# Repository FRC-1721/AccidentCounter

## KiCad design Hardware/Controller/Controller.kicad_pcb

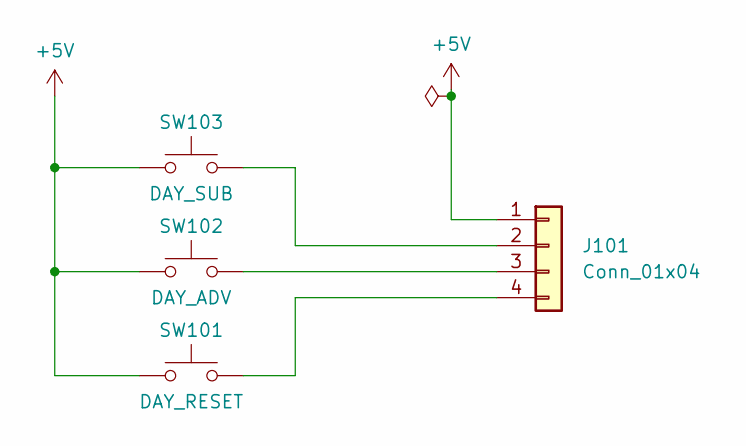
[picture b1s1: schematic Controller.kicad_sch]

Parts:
J101: Conn_01x04; SolderWire-1sqmm_1x04_P5.4mm_D1.4mm_OD2.7mm_Relief
SW101: DAY_RESET; SW_PUSH_6mm_H5mm
SW102: DAY_ADV; SW_PUSH_6mm_H5mm
SW103: DAY_SUB; SW_PUSH_6mm_H5mm

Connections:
+5V: J101.1, SW101.1, SW102.1, SW103.1
unnamed: J101.2, SW103.2
unnamed: J101.3, SW102.2
unnamed: J101.4, SW101.2

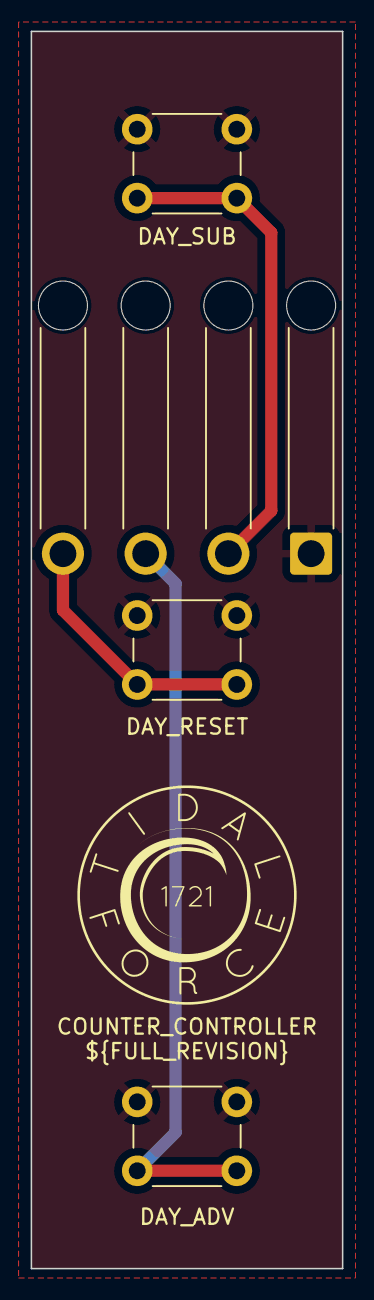
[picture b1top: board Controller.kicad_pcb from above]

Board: 2 copper layers, 20.3 x 80.8 mm, 4 parts (0 on the bottom side), 4 nets.

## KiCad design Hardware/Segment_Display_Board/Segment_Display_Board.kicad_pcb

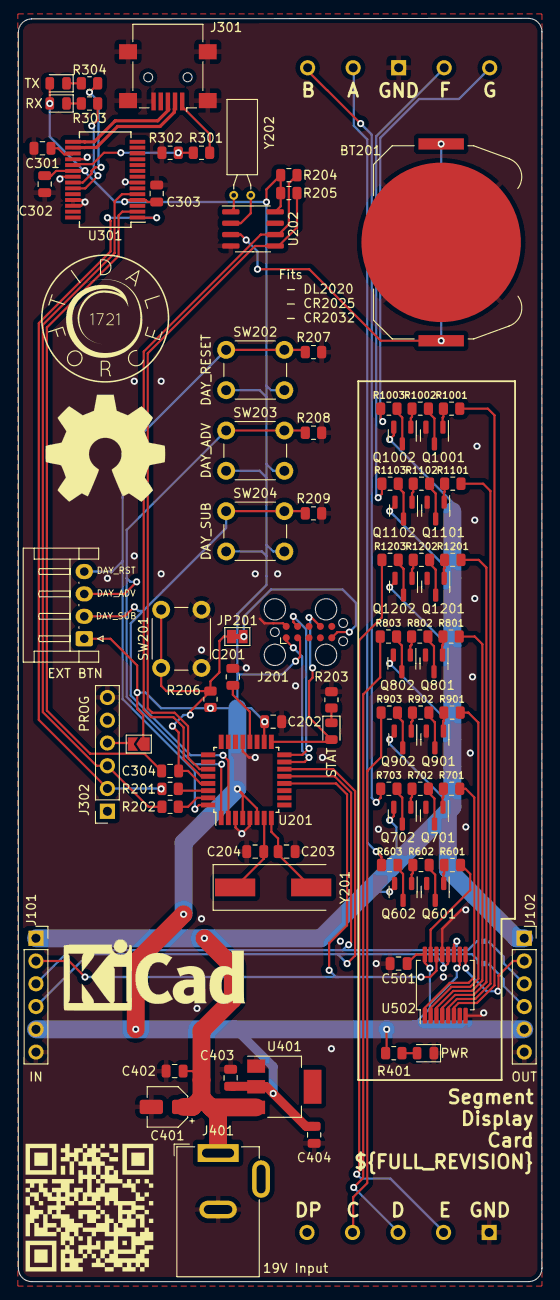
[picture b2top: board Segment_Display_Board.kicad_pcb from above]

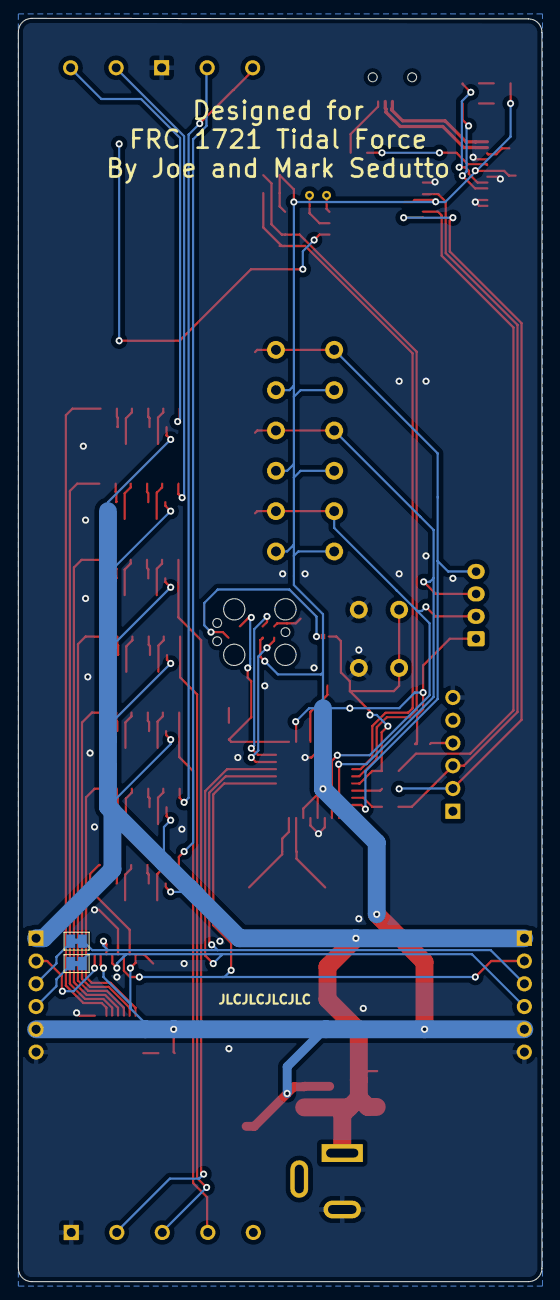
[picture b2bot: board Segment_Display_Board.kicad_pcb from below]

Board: 2 copper layers, 58.4 x 141.0 mm, 90 parts (2 on the bottom side), 84 nets.

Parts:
BT201: 3v; BatteryHolder_Keystone_3034_1x20mm
C201, C202: 100nf; C_0805_2012Metric
C203, C204: 22pf; C_0805_2012Metric
C301, C302, C303, C304, C402, C403, C501: 100nF; C_0805_2012Metric
C401: 10uf; CP_Elec_4x3
C404: 1uF; C_0805_2012Metric
D201: STAT; LED_0805_2012Metric
D301: RX; LED_0805_2012Metric
D302: TX; LED_0805_2012Metric
D401: PWR; LED_0805_2012Metric
J101: IN; PinSocket_1x06_P2.54mm_Vertical
J102: OUT; PinSocket_1x06_P2.54mm_Vertical
J201: Tag Connect; Tag-Connect_TC2050-IDC-FP_2x05_P1.27mm_Vertical
J202: EXT BTN; JST_EH_S4B-EH_1x04_P2.50mm_Horizontal
J301: USB_B_Micro; USB_Mini-B_Lumberg_2486_01_Horizontal
J302: PROG; PinSocket_1x06_P2.54mm_Vertical
J401: 19V Input; BarrelJack_GCT_DCJ200-10-A_Horizontal
JP201: RSTBridge; SolderJumper-2_P1.3mm_Bridged_Pad1.0x1.5mm
JP301: SolderJumper_2_Open; SolderJumper-2_P1.3mm_Open_TrianglePad1.0x1.5mm
JP501, JP502: SolderJumper_2_Bridged; SolderJumper-2_P1.3mm_Bridged_Pad1.0x1.5mm
Q601, Q701, Q801, Q901, Q1001, Q1101, Q1201: MMBT3904; SOT-23
Q602, Q702, Q802, Q902, Q1002, Q1102, Q1202: MMBT3906; SOT-23
R201, R202, R203, R206, R303, R304, R401: 1K; R_0805_2012Metric
R204, R205, R207, R208, R209, R302, R601, R701, R801, R901, R1001, R1101, R1201: 10K; R_0805_2012Metric
R301: 4K7; R_0805_2012Metric
R602, R702, R802, R902, R1002, R1102, R1202: 2K2; R_0805_2012Metric
R603, R703, R803, R903, R1003, R1103, R1203: 680R; R_0805_2012Metric
SW201: RESET; SW_PUSH_6mm_H5mm
SW202: DAY_RESET; SW_PUSH_6mm_H5mm
SW203: DAY_ADV; SW_PUSH_6mm_H5mm
SW204: DAY_SUB; SW_PUSH_6mm_H5mm
U201: ATmega328P-A; TQFP-32_7x7mm_P0.8mm
U202: DS1307Z+; SOIC-8_3.9x4.9mm_P1.27mm
U301: FT232RL; SSOP-28_5.3x10.2mm_P0.65mm
U401: NCV1117ST50T3G; SOT-223
U501: 5inSegment
U502: SN74HC595
Y201: 16mHz; Crystal_SMD_HC49-SD
Y202: 32.768kHz; Crystal_C38-LF_D3.0mm_L8.0mm_Horizontal

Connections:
+3.3V: C301.1, U301.17 (3V3OUT)
+5V: C202.1, C302.1, C303.1, C403.1, C404.1, C501.1, D301.2 (A), D302.2 (A), J101.5, J102.5, J201.2, J202.1, JP301.1 (A), R204.1, R205.1, R206.1, R401.1, SW202.2, SW203.2, SW204.2, U201.4 (VCC), U201.6 (VCC), U201.18 (AVCC), U202.8 (VCC), U301.4 (VCCIO), U301.20 (VCC), U401.2 (VO), U502.10 (SRCLR), U502.16 (VCC)
+19V: C401.1, C402.1, J101.1, J102.1, J401.1, Q602.2 (E), Q702.2 (E), Q802.2 (E), Q902.2 (E), Q1002.2 (E), Q1102.2 (E), Q1202.2 (E), U401.3 (VI)
/C_OUT: J101.3, JP502.1 (A), U201.13 (PB1), U502.11 (SRCLK)
/D_OUT: J101.2, U201.12 (PB0), U502.14 (SER)
/Display Card/CLOCK_OUT: J102.3, JP502.2 (B)
/Display Card/DATA_OUT: J102.2, U502.9 (QH')
/Display Card/LATCH_OUT: J102.4, JP501.2 (B)
/Display Card/SEG_A: R601.1, U502.15 (QA)
/Display Card/SEG_A_LAMP: R603.2, U501.2 (A)
/Display Card/SEG_B: R701.1, U502.1 (QB)
/Display Card/SEG_B_LAMP: R703.2, U501.1 (B)
/Display Card/SEG_C: R901.1, U502.2 (QC)
/Display Card/SEG_C_LAMP: R903.2, U501.7 (C)
/Display Card/SEG_D: R801.1, U502.3 (QD)
/Display Card/SEG_D_LAMP: R803.2, U501.8 (D)
/Display Card/SEG_E: R1201.1, U502.4 (QE)
/Display Card/SEG_E_LAMP: R1203.2, U501.9 (E)
/Display Card/SEG_F: R1101.1, U502.5 (QF)
/Display Card/SEG_F_LAMP: R1103.2, U501.4 (F)
/Display Card/SEG_G: R1001.1, U502.6 (QG)
/Display Card/SEG_G_LAMP: R1003.2, U501.5 (G)
/L_OUT: J101.4, JP501.1 (A), U201.14 (PB2), U502.12 (RCLK)
/MCU/DAY_ADVANCE: J202.3, R208.1, SW203.1, U201.1 (PD3)
/MCU/DAY_RESET: J202.4, R207.1, SW202.1, U201.32 (PD2)
/MCU/DAY_SUBTRACT: J202.2, R209.1, SW204.1, U201.2 (PD4)
/MCU/ICSP_MISO: J201.9, U201.16 (PB4)
/MCU/ICSP_MOSI: J201.1, U201.15 (PB3)
/MCU/ICSP_RST: J201.5, JP201.2 (B)
/MCU/ICSP_SCK: D201.2 (A), J201.7, U201.17 (PB5)
/MCU/RST: C304.1, JP201.1 (A), R206.2, SW201.1, U201.29 (~RESET/PC6)
/MCU/RXD: J302.2, R201.2, U301.1 (TXD)
/MCU/SCL: R204.2, U201.28 (PC5), U202.6 (SCL)
/MCU/SDA: R205.2, U201.27 (PC4), U202.5 (SDA)
/MCU/TXD: J302.3, R202.2, U301.5 (RXD)
/USB/USB+: J301.3 (D+), U301.15 (USBD+)
/USB/USB-: J301.2 (D-), U301.16 (USBD-)
GND: BT201.2 (-), C201.2, C202.2, C203.2, C204.2, C301.2, C302.2, C303.2, C401.2, C402.2, C403.2, C404.2, C501.2, D401.1 (K), J101.6, J102.6, J201.10, J301.5 (GND), J301.6 (Shield), J302.6, J401.2, Q601.2 (E), Q701.2 (E), Q801.2 (E), Q901.2 (E), Q1001.2 (E), Q1101.2 (E), Q1201.2 (E), R203.1, R207.2, R208.2, R209.2, R302.1, SW201.2, U201.3 (GND), U201.5 (GND), U201.21 (GND), U202.4 (GND), U301.7 (GND), U301.18 (GND), U301.21 (GND), U301.25 (AGND), U301.26 (TEST), U401.1 (GND), U501.3 (GND), U501.10 (GND), U502.8 (GND), U502.13 (OE)
unnamed: BT201.1 (+), U202.3 (VBAT)
unnamed: C201.1, U201.20 (AREF)
unnamed: C203.1, U201.8 (XTAL2/PB7), Y201.2
unnamed: C204.1, U201.7 (XTAL1/PB6), Y201.1
unnamed: C304.2, U301.2 (DTR)
unnamed: D201.1 (K), R203.2
unnamed: D301.1 (K), R303.2
unnamed: D302.1 (K), R304.1
unnamed: D401.2 (A), R401.2
unnamed: J302.4, JP301.2 (B)
unnamed: Q601.1 (B), R601.2
unnamed: Q601.3 (C), R602.1
unnamed: Q602.1 (B), R602.2
unnamed: Q602.3 (C), R603.1
unnamed: Q701.1 (B), R701.2
unnamed: Q701.3 (C), R702.1
unnamed: Q702.1 (B), R702.2
unnamed: Q702.3 (C), R703.1
unnamed: Q801.1 (B), R801.2
unnamed: Q801.3 (C), R802.1
unnamed: Q802.1 (B), R802.2
unnamed: Q802.3 (C), R803.1
unnamed: Q901.1 (B), R901.2
unnamed: Q901.3 (C), R902.1
unnamed: Q902.1 (B), R902.2
unnamed: Q902.3 (C), R903.1
unnamed: Q1001.1 (B), R1001.2
unnamed: Q1001.3 (C), R1002.1
unnamed: Q1002.1 (B), R1002.2
unnamed: Q1002.3 (C), R1003.1
unnamed: Q1101.1 (B), R1101.2
unnamed: Q1101.3 (C), R1102.1
unnamed: Q1102.1 (B), R1102.2
unnamed: Q1102.3 (C), R1103.1
unnamed: Q1201.1 (B), R1201.2
unnamed: Q1201.3 (C), R1202.1
unnamed: Q1202.1 (B), R1202.2
unnamed: Q1202.3 (C), R1203.1
unnamed: R201.1, U201.30 (PD0)
unnamed: R202.1, U201.31 (PD1)
unnamed: R301.1, R302.2, U301.19 (~RESET)
unnamed: R303.1, U301.23 (CBUS0)
unnamed: R304.2, U301.22 (CBUS1)
unnamed: U202.1 (X1), Y202.2
unnamed: U202.2 (X2), Y202.1
VBUS: J301.1 (VBUS), R301.2

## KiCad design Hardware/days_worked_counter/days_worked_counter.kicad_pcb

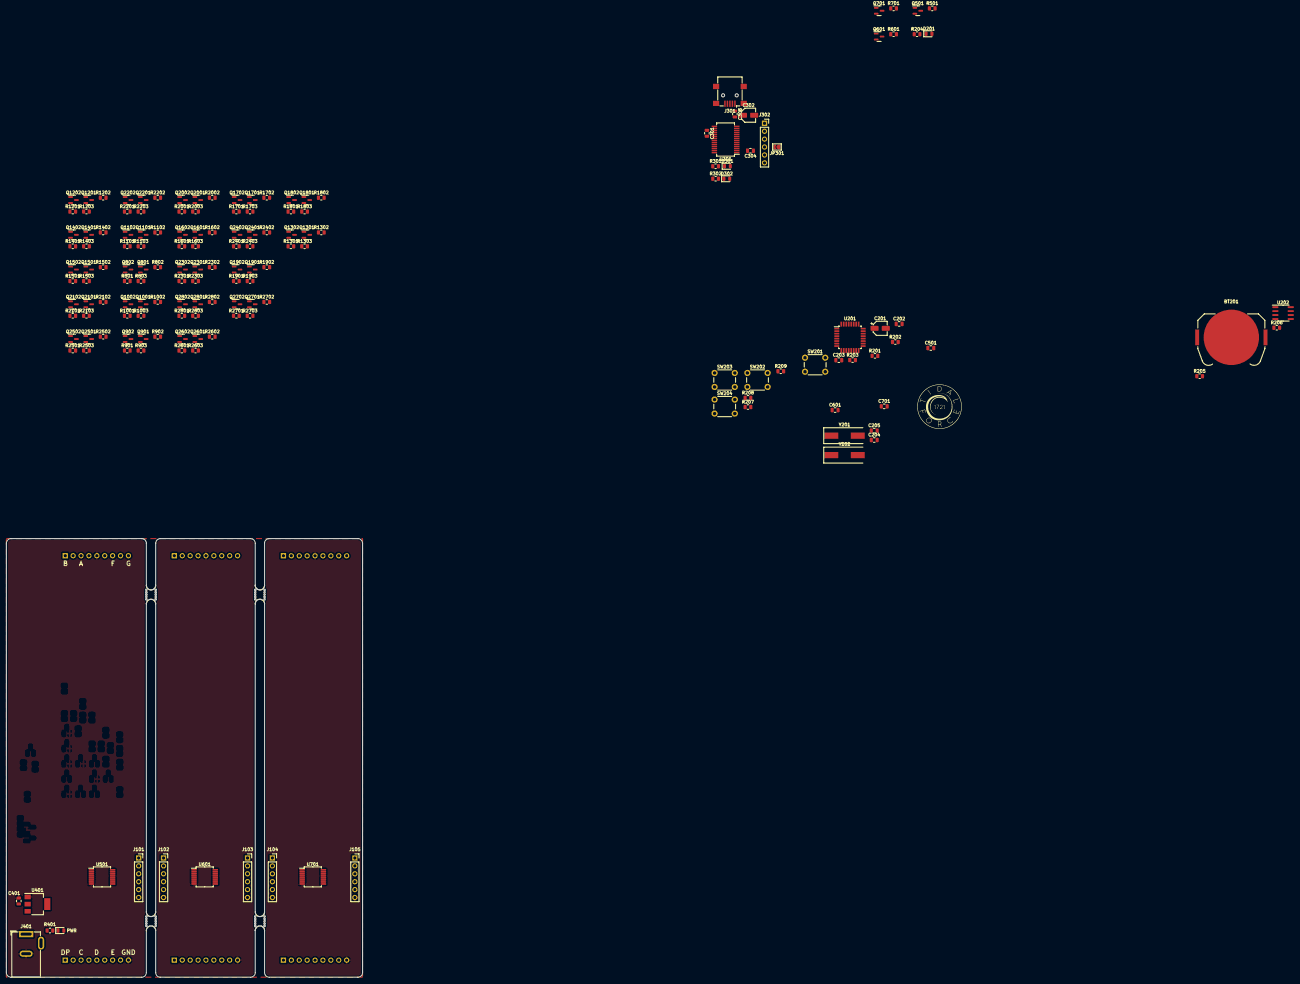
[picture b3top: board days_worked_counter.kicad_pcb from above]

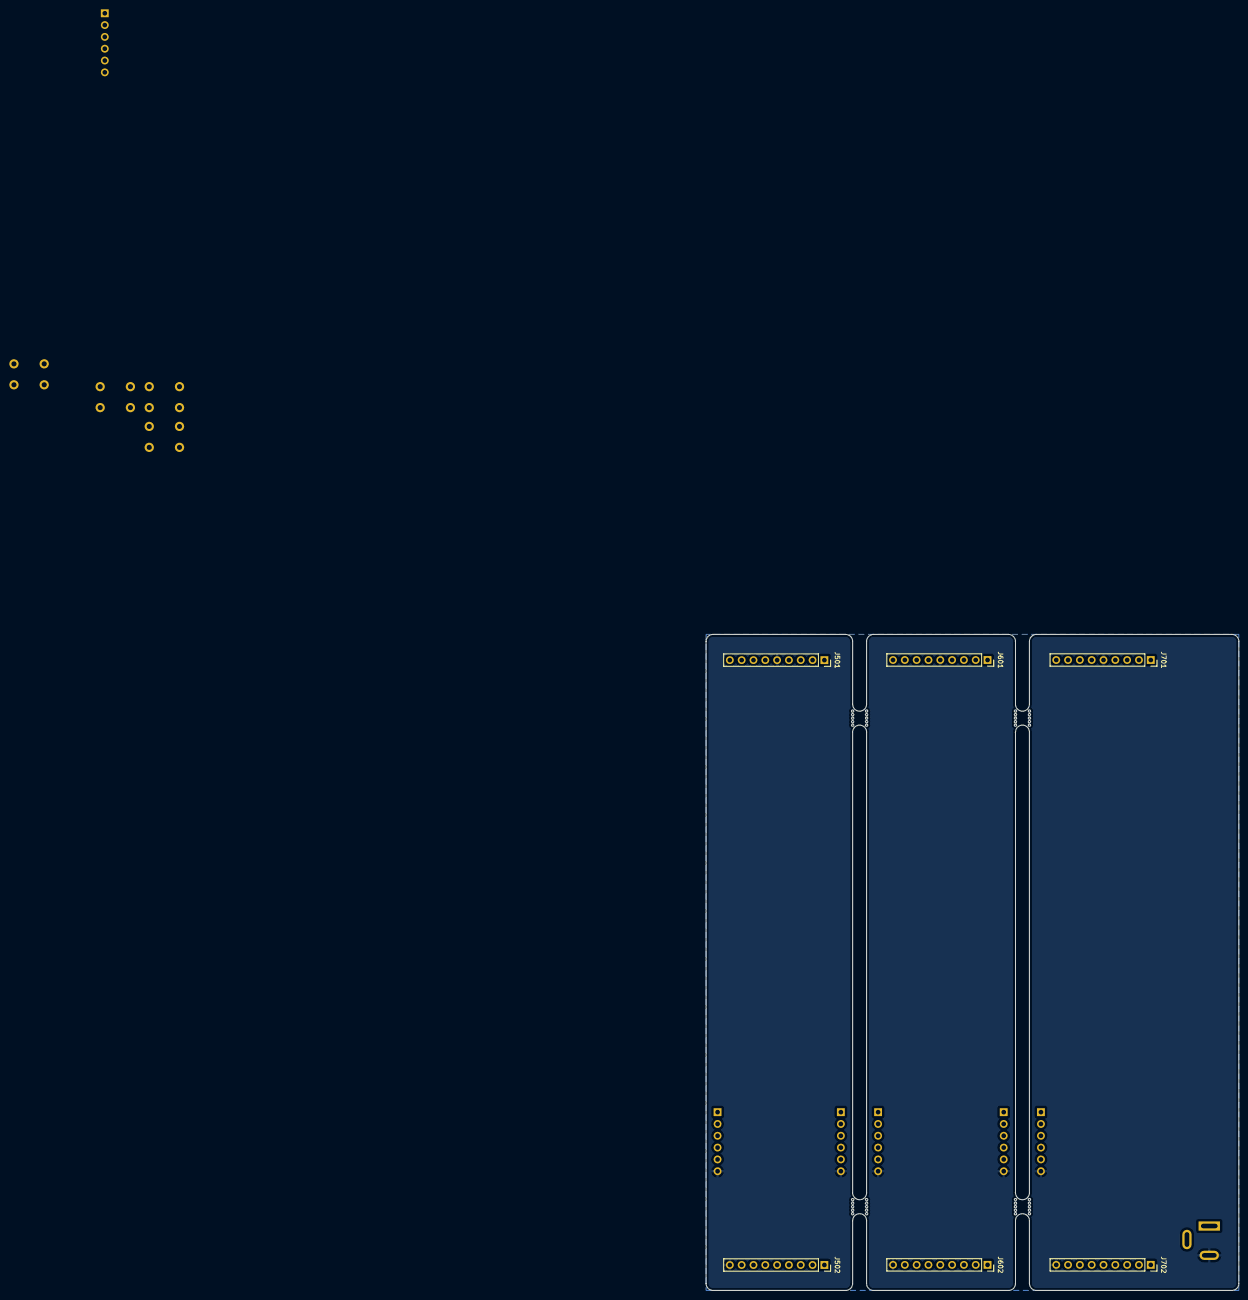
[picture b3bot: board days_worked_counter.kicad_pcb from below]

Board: 2 copper layers, 114.5 x 141.0 mm, 173 parts (6 on the bottom side), 170 nets, no tracks yet.

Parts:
BT201: 3v; BatteryHolder_Keystone_3034_1x20mm
C201, C302: 4.7uf; CP_Elec_4x3
C202, C203, C303: 100nf; C_0805_2012Metric
C204, C205: 22pf; C_0805_2012Metric
C301, C304, C401: 100nF; C_0805_2012Metric
C501, C601, C701: 10uF; C_0805_2012Metric
D201: STAT; LED_0805_2012Metric
D301: RX; LED_0805_2012Metric
D302: TX; LED_0805_2012Metric
D401: PWR; LED_0805_2012Metric
J101, J103, J105: OUT; PinSocket_1x06_P2.54mm_Vertical
J102, J104: IN; PinSocket_1x06_P2.54mm_Vertical
J301: USB_B_Micro; USB_Mini-B_Lumberg_2486_01_Horizontal
J302: PROG; PinSocket_1x06_P2.54mm_Vertical
J401: 19V Input; BarrelJack_GCT_DCJ200-10-A_Horizontal
J501, J601, J701: Top Conn; PinSocket_1x09_P2.54mm_Vertical
J502, J602, J702: Bottom Conn; PinSocket_1x09_P2.54mm_Vertical
JP301: SolderJumper_2_Open; SolderJumper-2_P1.3mm_Open_TrianglePad1.0x1.5mm
Q501, Q601, Q701, Q801, Q901, Q1001, Q1101, Q1201, Q1301, Q1401, Q1501, Q1601, Q1701, Q1801, Q1901, Q2001, Q2101, Q2201, Q2301, Q2401, Q2501, Q2601, Q2701, Q2801: MMBT3904; SOT-23
Q802, Q902, Q1002, Q1102, Q1202, Q1302, Q1402, Q1502, Q1602, Q1702, Q1802, Q1902, Q2002, Q2102, Q2202, Q2302, Q2402, Q2502, Q2602, Q2702, Q2802: MMBT3906; SOT-23
R201, R202, R203, R204, R301, R302, R401: 1K; R_0805_2012Metric
R205, R206, R207, R208, R209, R501, R601, R701, R801, R901, R1001, R1101, R1201, R1301, R1401, R1501, R1601, R1701, R1801, R1901, R2001, R2101, R2201, R2301, R2401, R2501, R2601, R2701, R2801: 10K; R_0805_2012Metric
R802, R902, R1002, R1102, R1202, R1302, R1402, R1502, R1602, R1702, R1802, R1902, R2002, R2102, R2202, R2302, R2402, R2502, R2602, R2702, R2802: 2K2; R_0805_2012Metric
R803, R903, R1003, R1103, R1203, R1303, R1403, R1503, R1603, R1703, R1803, R1903, R2003, R2103, R2203, R2303, R2403, R2503, R2603, R2703, R2803: 250R; R_0805_2012Metric
SW201: RESET; SW_PUSH_6mm_H5mm
SW202: DAY_RESET; SW_PUSH_6mm_H5mm
SW203: DAY_ADV; SW_PUSH_6mm_H5mm
SW204: DAY_SUB; SW_PUSH_6mm_H5mm
U201: ATmega328P-A; TQFP-32_7x7mm_P0.8mm
U202: DS1307Z+; SOIC-8_3.9x4.9mm_P1.27mm
U301: FT232RL; SSOP-28_5.3x10.2mm_P0.65mm
U401: LM1117-5.0; SOT-223
U501, U601, U701: SN74HC595
Y201: 16mHz; Crystal_SMD_HC49-SD
Y202: 32.768kHz; Crystal_SMD_HC49-SD
mouse-bite-3mm-slot, mouse-bite-3mm-slot#2, mouse-bite-3mm-slot#3, mouse-bite-3mm-slot#4: VAL**; mouse-bite-3mm-slot

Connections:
+3V3: C301.1, U301.17 (3V3OUT)
+5V: C201.1, C203.1, C401.1, C501.1, C601.1, C701.1, D301.2 (A), D302.2 (A), J101.5, J102.5, J103.5, J104.5, J105.5, JP301.1 (A), R201.1, R205.1, R206.1, R401.1, SW202.2, SW203.2, SW204.2, U201.4 (VCC), U201.6 (VCC), U201.18 (AVCC), U202.8 (VCC), U301.4 (VCCIO), U301.20 (VCC), U401.2 (VO), U501.10 (SRCLR), U501.16 (VCC), U601.10 (SRCLR), U601.16 (VCC), U701.10 (SRCLR), U701.16 (VCC)
+19V: J101.1, J102.1, J103.1, J104.1, J105.1, J401.1, Q802.2 (E), Q902.2 (E), Q1002.2 (E), Q1102.2 (E), Q1202.2 (E), Q1302.2 (E), Q1402.2 (E), Q1502.2 (E), Q1602.2 (E), Q1702.2 (E), Q1802.2 (E), Q1902.2 (E), Q2002.2 (E), Q2102.2 (E), Q2202.2 (E), Q2302.2 (E), Q2402.2 (E), Q2502.2 (E), Q2602.2 (E), Q2702.2 (E), Q2802.2 (E), U401.3 (VI)
/Display Card 0/CLOCK_IN: J101.3, U201.13 (PB1), U501.11 (SRCLK)
/Display Card 0/DATA_IN: U201.12 (PB0), U501.14 (SER)
/Display Card 0/DATA_OUT: J101.2, U501.9 (QH')
/Display Card 0/LATCH_IN: J101.4, U201.14 (PB2), U501.12 (RCLK)
/Display Card 0/SEG_A: R801.1, U501.15 (QA)
/Display Card 0/SEG_A_LAMP: J501.3, R803.2
/Display Card 0/SEG_B: Q501.1 (B), R501.1, R1101.1, U501.1 (QB)
/Display Card 0/SEG_B_LAMP: J501.1, R1103.2
/Display Card 0/SEG_C: R1501.1, U501.2 (QC)
/Display Card 0/SEG_C_LAMP: J502.3, R1503.2
/Display Card 0/SEG_D: R1401.1, U501.3 (QD)
/Display Card 0/SEG_D_LAMP: J502.5, R1403.2
/Display Card 0/SEG_E: R2201.1, U501.4 (QE)
/Display Card 0/SEG_E_LAMP: J502.7, R2203.2
/Display Card 0/SEG_F: R2101.1, U501.5 (QF)
/Display Card 0/SEG_F_LAMP: J501.7, R2103.2
/Display Card 0/SEG_G: R2001.1, U501.6 (QG)
/Display Card 0/SEG_G_LAMP: J501.9, R2003.2
/Display Card 1/CLOCK_IN: J102.3, J103.3, U601.11 (SRCLK)
/Display Card 1/DATA_IN: J102.2, U601.14 (SER)
/Display Card 1/DATA_OUT: J103.2, U601.9 (QH')
/Display Card 1/LATCH_IN: J102.4, J103.4, U601.12 (RCLK)
/Display Card 1/SEG_A: R901.1, U601.15 (QA)
/Display Card 1/SEG_A_LAMP: J601.3, R903.2
/Display Card 1/SEG_B: Q601.1 (B), R601.1, R1201.1, U601.1 (QB)
/Display Card 1/SEG_B_LAMP: J601.1, R1203.2
/Display Card 1/SEG_C: R1701.1, U601.2 (QC)
/Display Card 1/SEG_C_LAMP: J602.3, R1703.2
/Display Card 1/SEG_D: R1601.1, U601.3 (QD)
/Display Card 1/SEG_D_LAMP: J602.5, R1603.2
/Display Card 1/SEG_E: R2501.1, U601.4 (QE)
/Display Card 1/SEG_E_LAMP: J602.7, R2503.2
/Display Card 1/SEG_F: R2401.1, U601.5 (QF)
/Display Card 1/SEG_F_LAMP: J601.7, R2403.2
/Display Card 1/SEG_G: R2301.1, U601.6 (QG)
/Display Card 1/SEG_G_LAMP: J601.9, R2303.2
/Display Card 2/CLOCK_IN: J104.3, J105.3, U701.11 (SRCLK)
/Display Card 2/DATA_IN: J104.2, U701.14 (SER)
/Display Card 2/DATA_OUT: J105.2, U701.9 (QH')
/Display Card 2/LATCH_IN: J104.4, J105.4, U701.12 (RCLK)
/Display Card 2/SEG_A: R1001.1, U701.15 (QA)
/Display Card 2/SEG_A_LAMP: J701.3, R1003.2
/Display Card 2/SEG_B: Q701.1 (B), R701.1, R1301.1, U701.1 (QB)
/Display Card 2/SEG_B_LAMP: J701.1, R1303.2
/Display Card 2/SEG_C: R1901.1, U701.2 (QC)
/Display Card 2/SEG_C_LAMP: J702.3, R1903.2
/Display Card 2/SEG_D: R1801.1, U701.3 (QD)
/Display Card 2/SEG_D_LAMP: J702.5, R1803.2
/Display Card 2/SEG_E: R2801.1, U701.4 (QE)
/Display Card 2/SEG_E_LAMP: J702.7, R2803.2
/Display Card 2/SEG_F: R2701.1, U701.5 (QF)
/Display Card 2/SEG_F_LAMP: J701.7, R2703.2
/Display Card 2/SEG_G: R2601.1, U701.6 (QG)
/Display Card 2/SEG_G_LAMP: J701.9, R2603.2
/MCU/DAY_ADVANCE: R208.1, SW203.1, U201.1 (PD3)
/MCU/DAY_RESET: R207.1, SW202.1, U201.32 (PD2)
/MCU/DAY_SUBTRACT: R209.1, SW204.1, U201.2 (PD4)
/MCU/RST: C304.1, R201.2, SW201.1, U201.29 (~RESET/PC6)
/MCU/RXD: J302.2, R202.2, U301.1 (TXD)
/MCU/SCL: R205.2, U201.28 (PC5), U202.6 (SCL)
/MCU/SDA: R206.2, U201.27 (PC4), U202.5 (SDA)
/MCU/TXD: J302.3, R203.2, U301.5 (RXD)
GND: BT201.2 (-), C201.2, C202.2, C203.2, C204.2, C205.2, C301.2, C302.2, C303.2, C401.2, C501.2, C601.2, C701.2, D401.1 (K), J101.6, J102.6, J103.6, J104.6, J105.6, J301.5 (GND), J301.6 (Shield), J302.6, J401.2, J501.5, J502.9, J601.5, J602.9, J701.5, J702.9, Q501.2 (E), Q601.2 (E), Q701.2 (E), Q801.2 (E), Q901.2 (E), Q1001.2 (E), Q1101.2 (E), Q1201.2 (E), Q1301.2 (E), Q1401.2 (E), Q1501.2 (E), Q1601.2 (E), Q1701.2 (E), Q1801.2 (E), Q1901.2 (E), Q2001.2 (E), Q2101.2 (E), Q2201.2 (E), Q2301.2 (E), Q2401.2 (E), Q2501.2 (E), Q2601.2 (E), Q2701.2 (E), Q2801.2 (E), R204.1, R207.2, R208.2, R209.2, R501.2, R601.2, R701.2, SW201.2, U201.3 (GND), U201.5 (GND), U201.21 (GND), U202.4 (GND), U301.7 (GND), U301.18 (GND), U301.21 (GND), U301.25 (AGND), U301.26 (TEST), U401.1 (GND), U501.8 (GND), U501.13 (OE), U601.8 (GND), U601.13 (OE), U701.8 (GND), U701.13 (OE)
unnamed: BT201.1 (+), U202.3 (VBAT)
unnamed: C202.1, U201.20 (AREF)
unnamed: C204.1, U201.8 (XTAL2/PB7), Y201.2
unnamed: C205.1, U201.7 (XTAL1/PB6), Y201.1
unnamed: C304.2, U301.2 (DTR)
unnamed: D201.1 (K), R204.2
unnamed: D201.2 (A), U201.17 (PB5)
unnamed: D301.1 (K), R301.2
unnamed: D302.1 (K), R302.1
unnamed: D401.2 (A), R401.2
unnamed: J301.2 (D-), U301.16 (USBD-)
unnamed: J301.3 (D+), U301.15 (USBD+)
unnamed: J302.4, JP301.2 (B)
unnamed: Q801.1 (B), R801.2
unnamed: Q801.3 (C), R802.1
unnamed: Q802.1 (B), R802.2
unnamed: Q802.3 (C), R803.1
unnamed: Q901.1 (B), R901.2
unnamed: Q901.3 (C), R902.1
unnamed: Q902.1 (B), R902.2
unnamed: Q902.3 (C), R903.1
unnamed: Q1001.1 (B), R1001.2
unnamed: Q1001.3 (C), R1002.1
unnamed: Q1002.1 (B), R1002.2
unnamed: Q1002.3 (C), R1003.1
unnamed: Q1101.1 (B), R1101.2
unnamed: Q1101.3 (C), R1102.1
unnamed: Q1102.1 (B), R1102.2
unnamed: Q1102.3 (C), R1103.1
unnamed: Q1201.1 (B), R1201.2
unnamed: Q1201.3 (C), R1202.1
unnamed: Q1202.1 (B), R1202.2
unnamed: Q1202.3 (C), R1203.1
unnamed: Q1301.1 (B), R1301.2
unnamed: Q1301.3 (C), R1302.1
unnamed: Q1302.1 (B), R1302.2
unnamed: Q1302.3 (C), R1303.1
unnamed: Q1401.1 (B), R1401.2
unnamed: Q1401.3 (C), R1402.1
unnamed: Q1402.1 (B), R1402.2
unnamed: Q1402.3 (C), R1403.1
unnamed: Q1501.1 (B), R1501.2
unnamed: Q1501.3 (C), R1502.1
unnamed: Q1502.1 (B), R1502.2
unnamed: Q1502.3 (C), R1503.1
unnamed: Q1601.1 (B), R1601.2
unnamed: Q1601.3 (C), R1602.1
unnamed: Q1602.1 (B), R1602.2
unnamed: Q1602.3 (C), R1603.1
unnamed: Q1701.1 (B), R1701.2
unnamed: Q1701.3 (C), R1702.1
unnamed: Q1702.1 (B), R1702.2
unnamed: Q1702.3 (C), R1703.1
unnamed: Q1801.1 (B), R1801.2
unnamed: Q1801.3 (C), R1802.1
unnamed: Q1802.1 (B), R1802.2
unnamed: Q1802.3 (C), R1803.1
unnamed: Q1901.1 (B), R1901.2
unnamed: Q1901.3 (C), R1902.1
unnamed: Q1902.1 (B), R1902.2
unnamed: Q1902.3 (C), R1903.1
unnamed: Q2001.1 (B), R2001.2
unnamed: Q2001.3 (C), R2002.1
unnamed: Q2002.1 (B), R2002.2
unnamed: Q2002.3 (C), R2003.1
unnamed: Q2101.1 (B), R2101.2
unnamed: Q2101.3 (C), R2102.1
unnamed: Q2102.1 (B), R2102.2
unnamed: Q2102.3 (C), R2103.1
unnamed: Q2201.1 (B), R2201.2
unnamed: Q2201.3 (C), R2202.1
unnamed: Q2202.1 (B), R2202.2
unnamed: Q2202.3 (C), R2203.1
unnamed: Q2301.1 (B), R2301.2
unnamed: Q2301.3 (C), R2302.1
unnamed: Q2302.1 (B), R2302.2
unnamed: Q2302.3 (C), R2303.1
unnamed: Q2401.1 (B), R2401.2
unnamed: Q2401.3 (C), R2402.1
unnamed: Q2402.1 (B), R2402.2
unnamed: Q2402.3 (C), R2403.1
unnamed: Q2501.1 (B), R2501.2
unnamed: Q2501.3 (C), R2502.1
unnamed: Q2502.1 (B), R2502.2
unnamed: Q2502.3 (C), R2503.1
unnamed: Q2601.1 (B), R2601.2
unnamed: Q2601.3 (C), R2602.1
unnamed: Q2602.1 (B), R2602.2
unnamed: Q2602.3 (C), R2603.1
unnamed: Q2701.1 (B), R2701.2
unnamed: Q2701.3 (C), R2702.1
unnamed: Q2702.1 (B), R2702.2
unnamed: Q2702.3 (C), R2703.1
unnamed: Q2801.1 (B), R2801.2
unnamed: Q2801.3 (C), R2802.1
unnamed: Q2802.1 (B), R2802.2
unnamed: Q2802.3 (C), R2803.1
unnamed: R202.1, U201.30 (PD0)
unnamed: R203.1, U201.31 (PD1)
unnamed: R301.1, U301.23 (CBUS0)
unnamed: R302.2, U301.22 (CBUS1)
unnamed: U202.1 (X1), Y202.2
unnamed: U202.2 (X2), Y202.1
VBUS: C302.1, C303.1, J301.1 (VBUS)

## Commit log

2021-07-31 Added all of the thing
2021-07-31 Fixed day one patch
2021-07-31 Disable the fluff
2021-07-31 rename branch
2021-07-31 Code bjorked
2021-07-31 Red!
2021-12-14 Major boilerplate + add all snap code
2021-12-14 Remove unused
2021-12-14 Cleanup
2021-12-14 not much fixed
2021-12-14 This, kinda works?
2022-06-24 Create base drawings + sch for new brd
2022-06-24 Add tidal force
2022-06-24 Cleanup more stuff
2022-06-24 Add all the cool stuff
2022-06-27 Even more stuff
2022-06-27 Add drawings and pin placements
2022-06-27 Include 7 Segment Bracket
2022-06-27 Add stuff
2022-06-28 get input from @ka2qfx
2022-06-28 Thank @ka2qfx for fixups!
2022-06-28 Add readme
2022-06-28 Change direction
2022-06-28 With thanks to @ka2qfx
2022-06-28 move all
2022-06-28 move all again
2022-06-28 Steps for a RC1
2022-06-28 Fix stuff i guess goodnight"
2022-06-28 Minor fixups
2022-06-28 Prep for release system
2022-06-28 Add a bunch more great stuff
2022-06-28 Add firmware filler
2022-06-28 Place hardware orders
2022-06-28 Fix release
2022-06-28 Add a nice outline so you know what a client brd needs
2022-06-28 Use a different regulator
2022-06-28 include fixups fro EE
2022-06-29 Bump readme
2022-07-05 Nothing
2022-07-18 Add stencil and small text fixup
2022-07-18 This firmware works
2022-07-18 Flashy
2022-07-18 Silkscreen cleanup
2022-07-19 Add last
2022-07-19 unadd
2022-07-20 Fixup some stuff
2022-07-20 Works enough to do something basic
2022-07-21 more stuff, fried a chip
2022-07-21 Include battery info
2022-07-21 Clock still does not work lol~
2022-07-21 Ok, this is pretty awesome
2022-07-21 Fix a bug where if there was noise on the serial wires it would cause a soft reset
2022-07-21 Fix another bug where you could underflow by spamming day_sub
2022-07-21 Include fancy ICSP programmer (lol)
2022-07-22 Fix a inturrupt based bug:
2022-07-22 Add poster templates
2022-07-22 lil things
2022-07-25 Put together a slightly better firmware and remove some extra bloat, did not find source of the 12 bug..
2022-07-25 Bump poster
2022-07-25 Fixup poster
2022-07-25 Add instructions
2022-07-25 make more obvious
2022-07-26 Add matt's suggestions
2022-07-26 Minor cleanups
2022-07-26 Minor patch on fw workflow
2022-07-26 Add a poster holder
2022-07-27 If i ever have to make another poster it will look a lot nicer
2022-07-27 Include watchdog incase of... anything
2022-07-27 cleanup watchdog
2022-07-28 Use new 5in symbol and footprint
2022-07-31 Change package for 1uF capacitor
2022-08-01 Add static content
2022-08-02 Build for JLCPCB too
2022-08-02 Remove anchors?
2022-08-02 Fixup
2022-08-12 Add breakout for external buttons
2022-08-12 Fix DRC
2022-08-16 Add JLCPCB staging to actual release too
2022-08-16 Move jumper desig
2022-09-01 Update static picture
2022-09-02 Add yt link
2022-10-17 Fix typo
2022-11-23 Possible rewire
2022-12-14 Fixup! Fixes an upstream bug where reference values attached to parts were not included on silkscreen.
2022-12-16 Create some doomsday clock stuff
2023-06-22 Fix a bug where displays with less than 3 chars could not display E, Er or Err correctly
2023-10-19 Add new board for remote
2023-10-19 Bump kibot
2023-10-19 Update node and fix dev-publish
2023-10-19 Add routes
2023-10-19 bump instructions
2023-10-19 Remote Board (#8)
    All checks pass, lets merge this
